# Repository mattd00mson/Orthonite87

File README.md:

# Orthonite87
Orthonite87 is a 87 key Ortholinear keyboard.

## Subheader

Unlock the full potential of ortholinear

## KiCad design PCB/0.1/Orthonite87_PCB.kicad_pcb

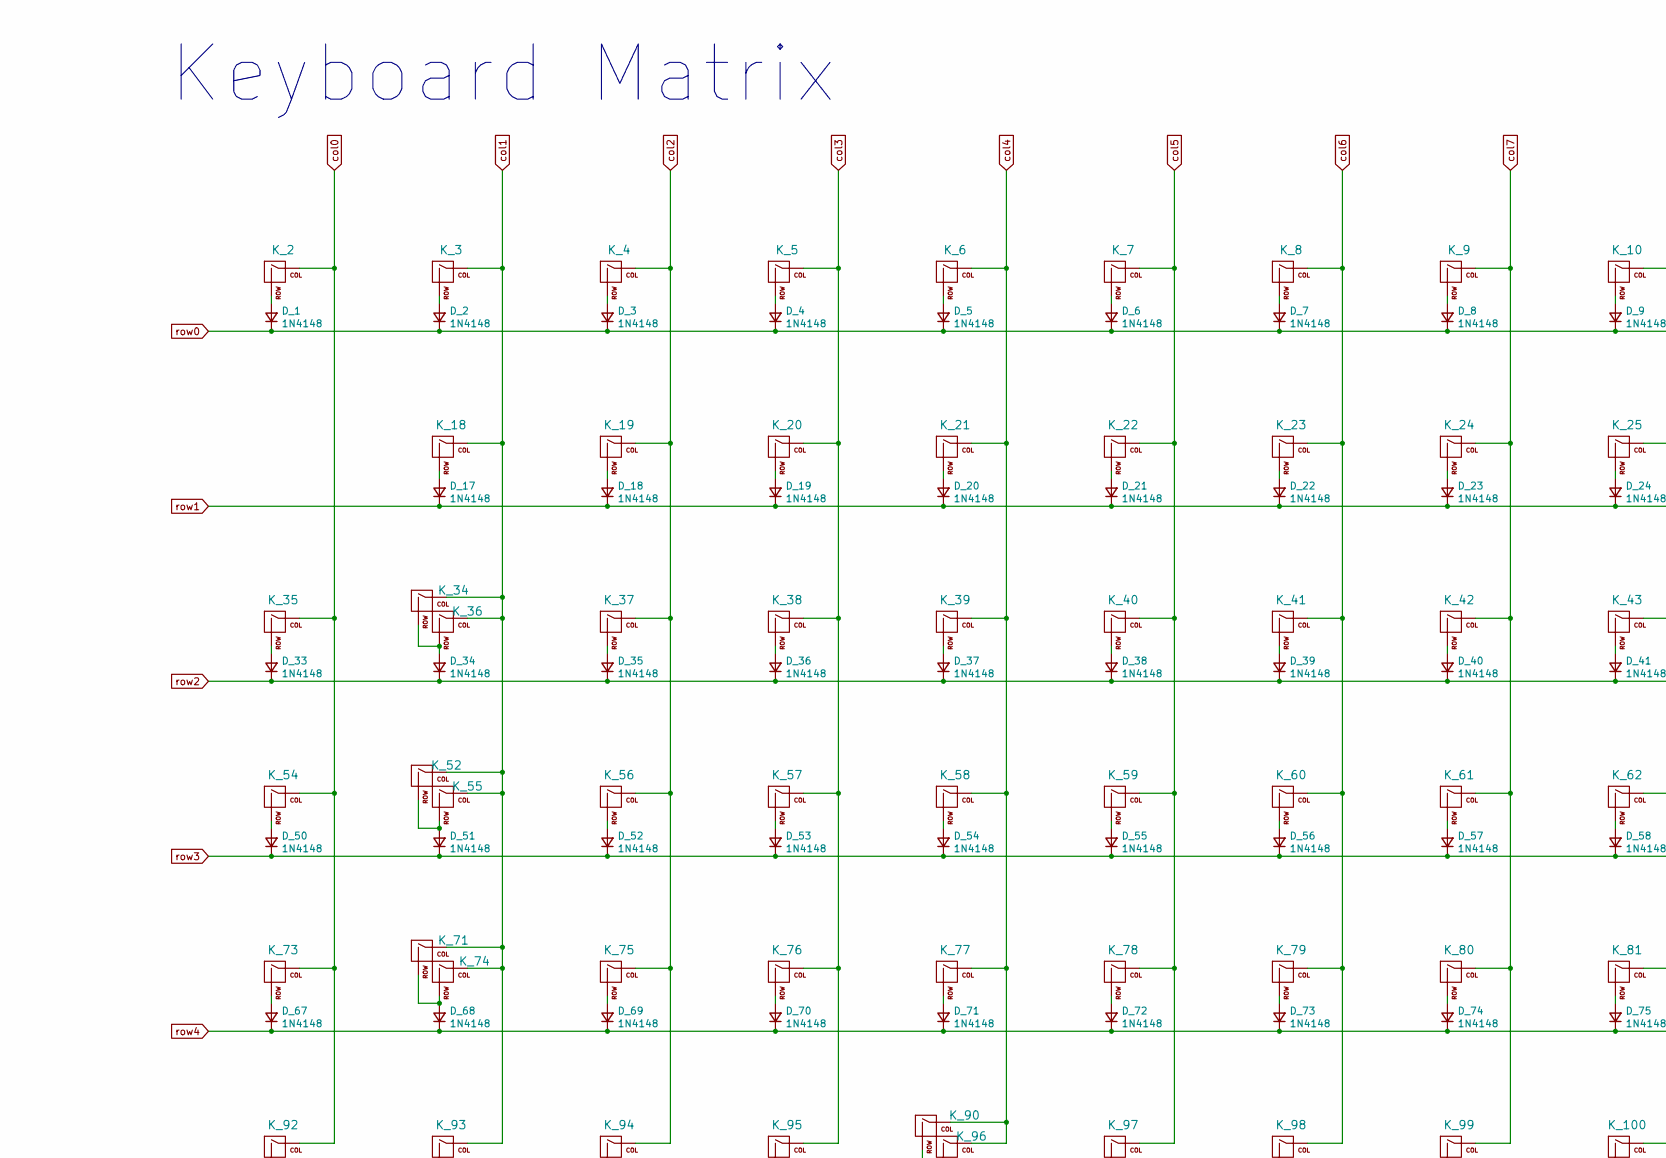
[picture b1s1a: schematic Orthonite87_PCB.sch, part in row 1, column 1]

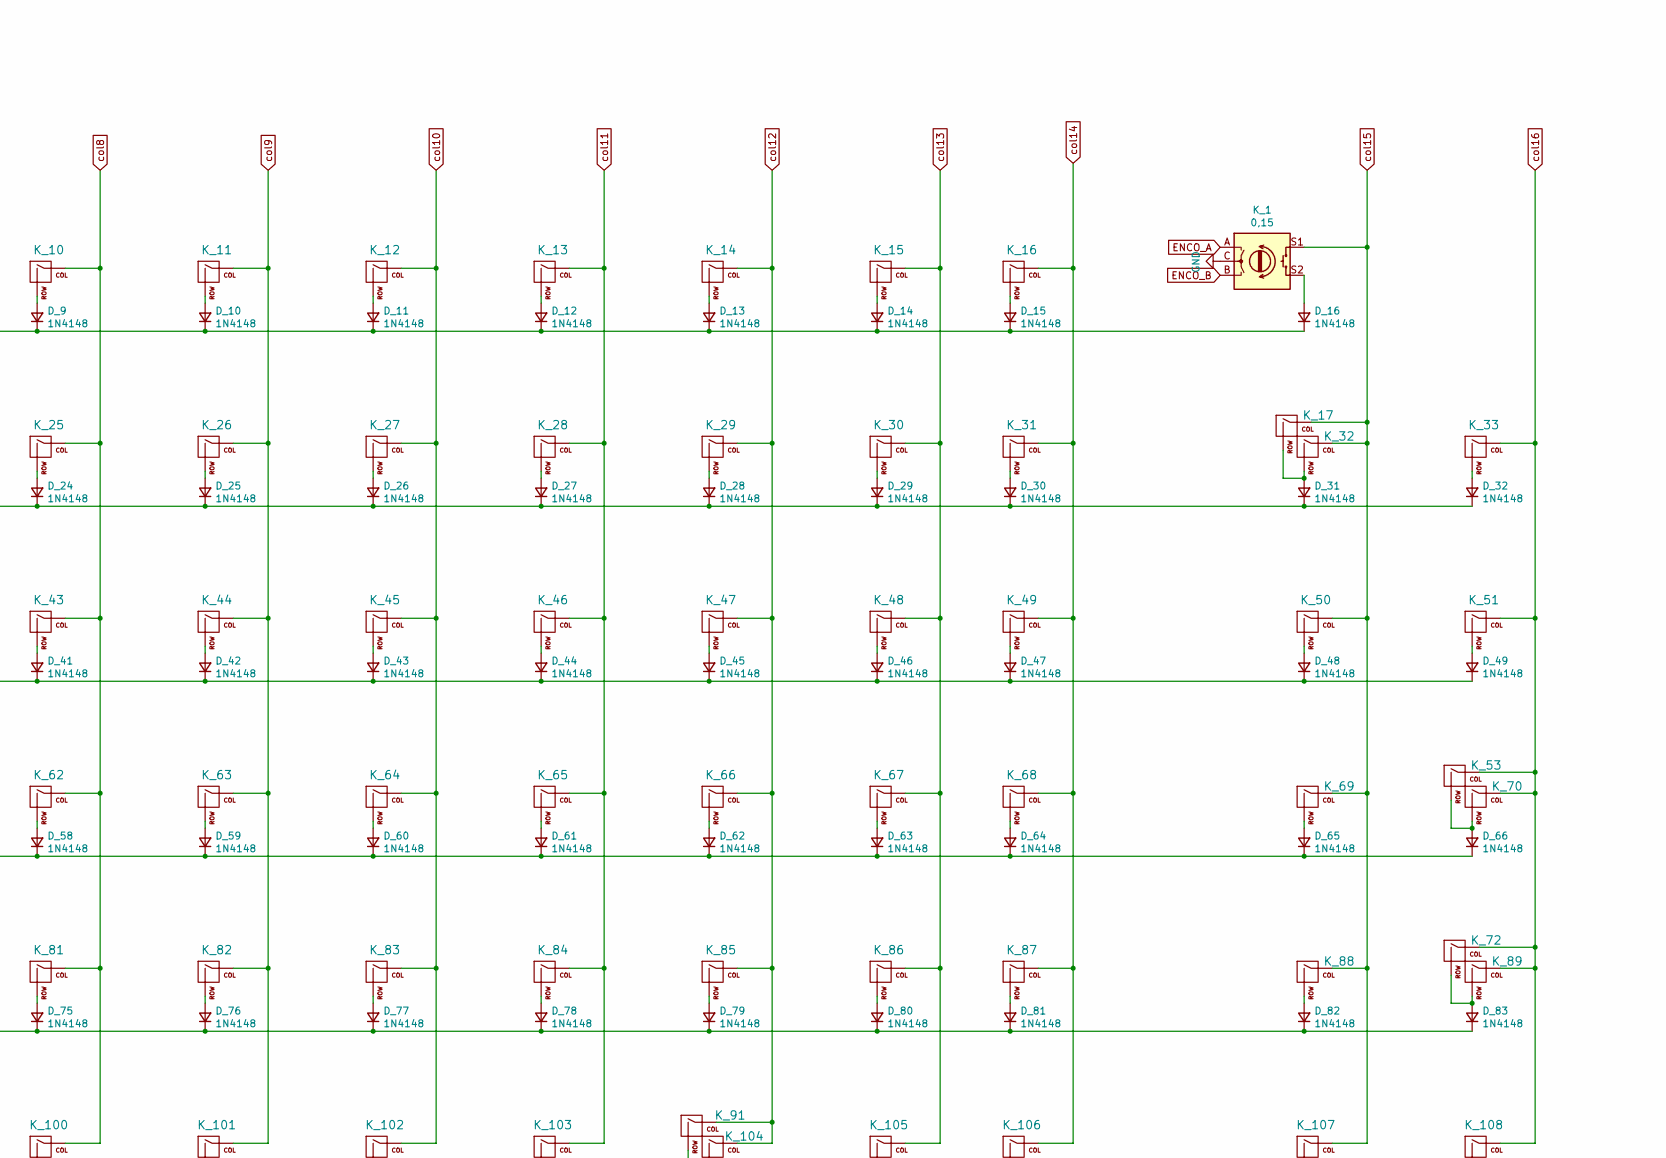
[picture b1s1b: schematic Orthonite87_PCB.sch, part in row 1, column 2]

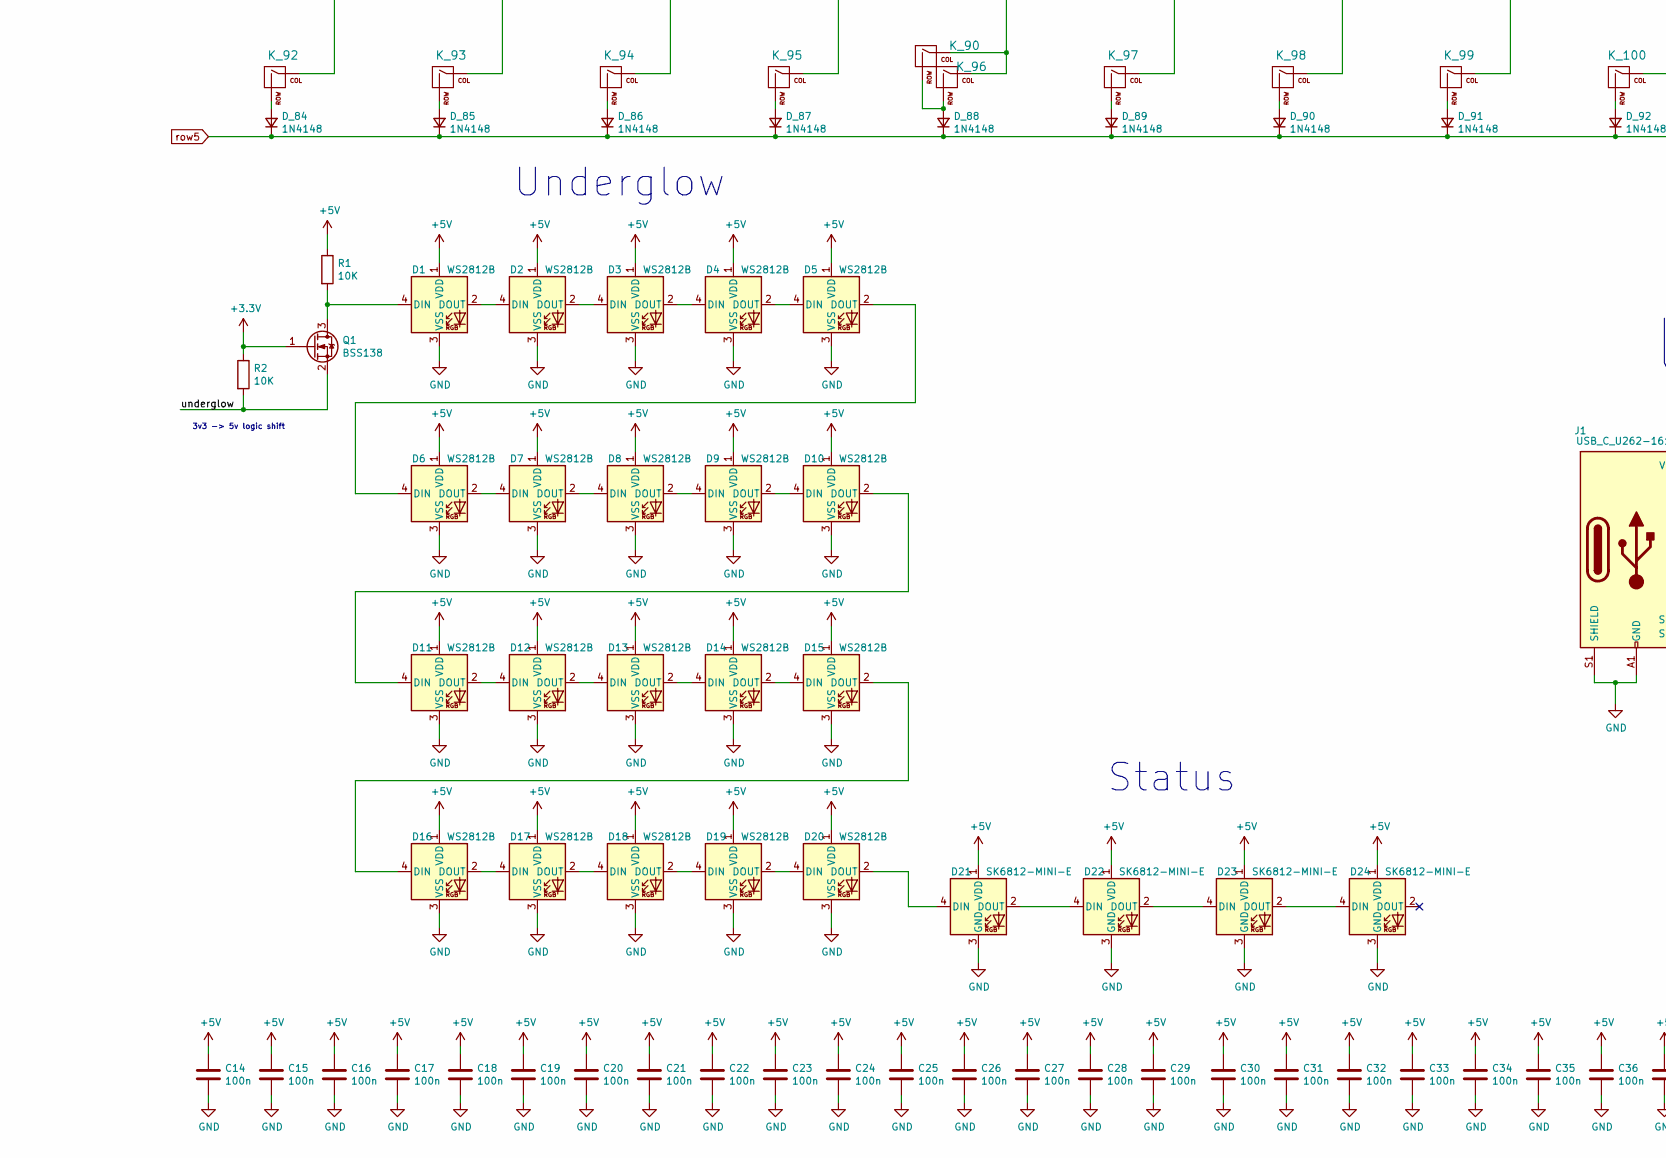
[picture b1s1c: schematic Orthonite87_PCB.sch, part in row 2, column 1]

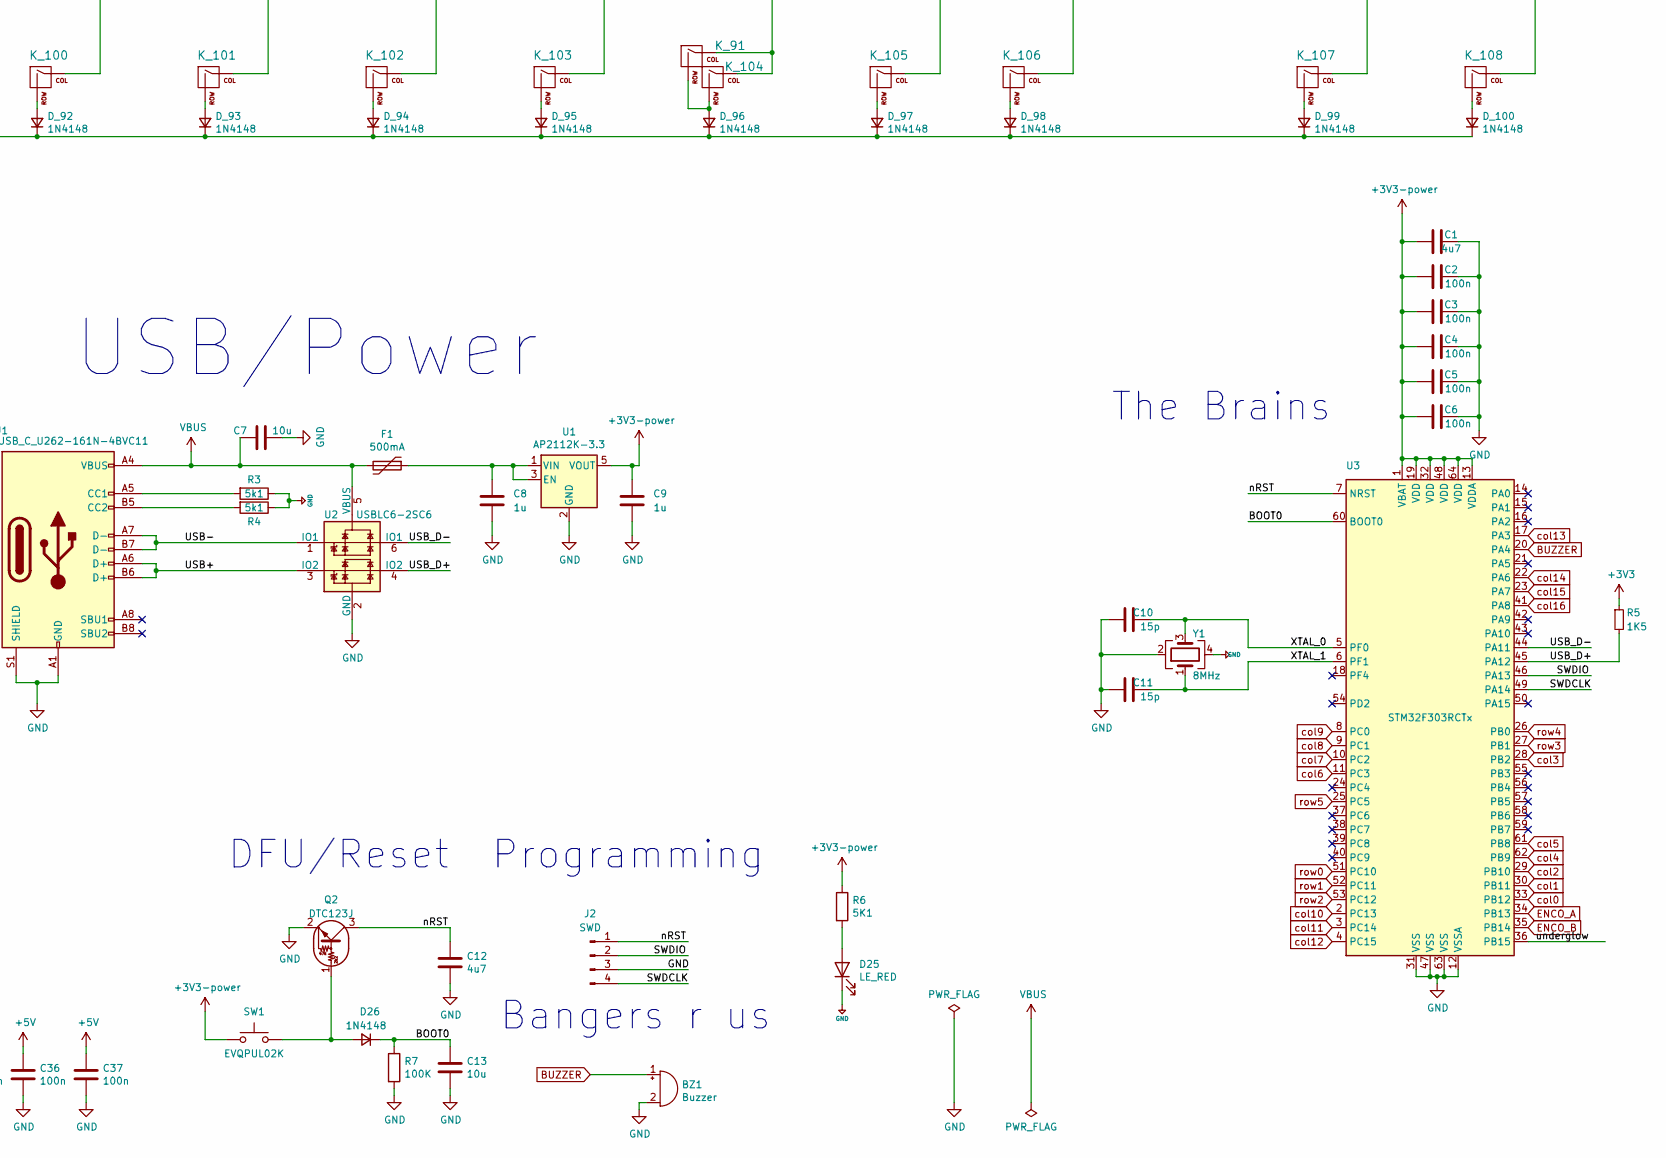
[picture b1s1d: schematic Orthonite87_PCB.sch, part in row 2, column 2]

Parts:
BZ1: Buzzer; Buzzer_Murata_PKMCS0909E4000-R1; MPN PKMCS0909E4000-R1; LCSC C910763
C1, C12: 4u7; C_1608; MPN CL10A475KO8NNNC; JLCSMT C19666
C2, C3, C4, C5, C6: 100n; C_1608; MPN CC0603KRX7R9BB104; JLCSMT C14663
C7, C13: 10u; C_1608; MPN CL10A106KP8NNNC; JLCSMT C19702
C8, C9: 1u; C_1608; MPN CL10A105KB8NNNC; LCSC C15849
C10, C11: 15p; C_1608; MPN CL10C150JB8NNNC; JLCSMT C1644
C14, C15, C16, C17, C18, C19, C20, C21, C22, C23, C24, C25, C26, C27, C28, C29, C30, C31, C32, C33, C34, C35, C36, C37: 100n; C_1608; MPN CC0603KRX7R9BB104; LCSC C14663
D1, D2, D3, D4, D5, D6, D7, D8, D9, D10, D11, D12, D13, D14, D15, D16, D17, D18, D19, D20: WS2812B; LED_WS2812B_PLCC4_5.0x5.0mm_P3.2mm; MPN WS2812B-B; LCSC C114586
D21, D22, D23, D24: SK6812-MINI-E; SK8612-MINI-E; MPN SK6812-MINI-E
D25: LE_RED; LED_0603_1608Metric_45_noSilk; MPN KT-0603R; JLCSMT C2286
D26: 1N4148; SOD3716X135N; MPN 1N4148W; JLCSMT C81598
D_1, D_2, D_3, D_4, D_5, D_6, D_7, D_8, D_9, D_10, D_11, D_12, D_13, D_14, D_15, D_16, D_17, D_18, D_19, D_20, D_21, D_22, D_23, D_24, D_25, D_26, D_27, D_28, D_29, D_30, D_31, D_32, D_33, D_34, D_35, D_36, D_37, D_38, D_39, D_40, D_41, D_42, D_43, D_44, D_45, D_46, D_47, D_48, D_49, D_50, D_51, D_52, D_53, D_54, D_55, D_56, D_57, D_58, D_59, D_60, D_61, D_62, D_63, D_64, D_65, D_66, D_67, D_68, D_69, D_70, D_71, D_72, D_73, D_74, D_75, D_76, D_77, D_78, D_79, D_80, D_81, D_82, D_83, D_84, D_85, D_86, D_87, D_88, D_89, D_90, D_91, D_92, D_93, D_94, D_95, D_96, D_97, D_98, D_99, D_100: 1N4148; SOD3716X135N; MPN 1N4148W; JLCSMT C81598
F1: 500mA; Fuse_0805_2012Metric; MPN SMD0805-050; JLCSMT C66452
J1: USB_C_U262-161N-4BVC11; MPN U262-161N-4BVC11; LCSC C319148
J2: SWD; STM_4_PIN_THT_Staggered
K_1: 0,15; MX_KEYSWITCH_ENCODER
K_2: 0,0; MXOnly-1U-NoLED
K_3: 0,1; MXOnly-1U-NoLED
K_4: 0,2; MXOnly-1U-NoLED
K_5: 0,3; MXOnly-1U-NoLED
K_6: 0,4; MXOnly-1U-NoLED
K_7: 0,5; MXOnly-1U-NoLED
K_8: 0,6; MXOnly-1U-NoLED
K_9: 0,7; MXOnly-1U-NoLED
K_10: 0,8; MXOnly-1U-NoLED
K_11: 0,9; MXOnly-1U-NoLED
K_12: 0,10; MXOnly-1U-NoLED
K_13: 0,11; MXOnly-1U-NoLED
K_14: 0,12; MXOnly-1U-NoLED
K_15: 0,13; MXOnly-1U-NoLED
K_16: 0,14; MXOnly-1U-NoLED
K_17: 1,15; MXOnly-1U-NoLED
K_18: 1,1; MXOnly-1U-NoLED
K_19: 1,2; MXOnly-1U-NoLED
K_20: 1,3; MXOnly-1U-NoLED
K_21: 1,4; MXOnly-1U-NoLED
K_22: 1,5; MXOnly-1U-NoLED
K_23: 1,6; MXOnly-1U-NoLED
K_24: 1,7; MXOnly-1U-NoLED
K_25: 1,8; MXOnly-1U-NoLED
K_26: 1,9; MXOnly-1U-NoLED
K_27: 1,10; MXOnly-1U-NoLED
K_28: 1,11; MXOnly-1U-NoLED
K_29: 1,12; MXOnly-1U-NoLED
K_30: 1,13; MXOnly-1U-NoLED
K_31: 1,14; MXOnly-1U-NoLED
K_32: 1,16; MXOnly-2U-NoLED
K_33: 1,17; MXOnly-1U-NoLED
K_34: 2,1; MXOnly-1U-NoLED
K_35: 2,0; MXOnly-1U-NoLED
K_36: 2,2; MXOnly-2U-NoLED
K_37: 2,3; MXOnly-1U-NoLED
K_38: 2,4; MXOnly-1U-NoLED
K_39: 2,5; MXOnly-1U-NoLED
K_40: 2,6; MXOnly-1U-NoLED
K_41: 2,7; MXOnly-1U-NoLED
K_42: 2,8; MXOnly-1U-NoLED
K_43: 2,9; MXOnly-1U-NoLED
K_44: 2,10; MXOnly-1U-NoLED
K_45: 2,11; MXOnly-1U-NoLED
K_46: 2,12; MXOnly-1U-NoLED
K_47: 2,13; MXOnly-1U-NoLED
K_48: 2,14; MXOnly-1U-NoLED
K_49: 2,15; MXOnly-1U-NoLED
K_50: 2,16; MXOnly-1U-NoLED
K_51: 2,17; MXOnly-1U-NoLED
K_52: 3,1; MXOnly-1U-NoLED
K_53: 3,17; MXOnly-1U-NoLED
K_54: 3,0; MXOnly-1U-NoLED
K_55: 3,2; MXOnly-2U-NoLED
K_56: 3,3; MXOnly-1U-NoLED
K_57: 3,4; MXOnly-1U-NoLED
K_58: 3,5; MXOnly-1U-NoLED
K_59: 3,6; MXOnly-1U-NoLED
K_60: 3,7; MXOnly-1U-NoLED
K_61: 3,8; MXOnly-1U-NoLED
K_62: 3,9; MXOnly-1U-NoLED
K_63: 3,10; MXOnly-1U-NoLED
K_64: 3,11; MXOnly-1U-NoLED
K_65: 3,12; MXOnly-1U-NoLED
K_66: 3,13; MXOnly-1U-NoLED
K_67: 3,14; MXOnly-1U-NoLED
K_68: 3,15; MXOnly-1U-NoLED
K_69: 3,16; MXOnly-1U-NoLED
K_70: 3,18; MXOnly-2U-NoLED
K_71: 4,1; MXOnly-1U-NoLED
K_72: 4,17; MXOnly-1U-NoLED
K_73: 4,0; MXOnly-1U-NoLED
K_74: 4,2; MXOnly-2U-NoLED
K_75: 4,3; MXOnly-1U-NoLED
K_76: 4,4; MXOnly-1U-NoLED
K_77: 4,5; MXOnly-1U-NoLED
K_78: 4,6; MXOnly-1U-NoLED
K_79: 4,7; MXOnly-1U-NoLED
K_80: 4,8; MXOnly-1U-NoLED
K_81: 4,9; MXOnly-1U-NoLED
K_82: 4,10; MXOnly-1U-NoLED
K_83: 4,11; MXOnly-1U-NoLED
K_84: 4,12; MXOnly-1U-NoLED
K_85: 4,13; MXOnly-1U-NoLED
K_86: 4,14; MXOnly-1U-NoLED
K_87: 4,15; MXOnly-1U-NoLED
K_88: 4,16; MXOnly-1U-NoLED
K_89: 4,18; MXOnly-2U-NoLED
K_90: 5,4; MXOnly-1U-NoLED
K_91: 5,13; MXOnly-1U-NoLED
K_92: 5,0; MXOnly-1U-NoLED
K_93: 5,1; MXOnly-1U-NoLED
K_94: 5,2; MXOnly-1U-NoLED
K_95: 5,3; MXOnly-1U-NoLED
K_96: 5,5; MXOnly-3U-ReversedStabilizers-NoLED
K_97: 5,6; MXOnly-1U-NoLED
K_98: 5,7; MXOnly-1U-NoLED
K_99: 5,8; MXOnly-1U-NoLED
K_100: 5,9; MXOnly-1U-NoLED
K_101: 5,10; MXOnly-1U-NoLED
K_102: 5,11; MXOnly-1U-NoLED
K_103: 5,12; MXOnly-1U-NoLED
K_104: 5,14; MXOnly-3U-ReversedStabilizers-NoLED
K_105: 5,15; MXOnly-1U-NoLED
K_106: 5,16; MXOnly-1U-NoLED
K_107: 5,17; MXOnly-1U-NoLED
K_108: 5,18; MXOnly-1U-NoLED
Q1: BSS138; SOT-23; MPN BSS138LT1G; LCSC C82045
Q2: DTC123J; SOT95P280X100-3N; MPN DTC123JKAT146; JLCSMT C111724
R1, R2: 10K; R_1608; MPN 0603WAF1002T5E; LCSC C25804
R3, R4: 5k1; R_1608; MPN 0603WAF5101T5E; JLCSMT C23186
R5: 1K5; R_0603_1608Metric
R6: 5K1; R_1608; MPN 0603WAF5101T5E; JLCSMT C23186
R7: 100K; R_1608; MPN 0603WAF1003T5E; JLCSMT C25803
SW1: EVQPUL02K; Panasonic_EVQPUL_EVQPUC; MPN EVQPUL02K; LCSC C79175
U1: AP2112K-3.3; SOT-23-5; MPN AP2112K-3.3TRG1; LCSC C51118
U2: USBLC6-2SC6; SOT-23-6; MPN USBLC6-2SC6; JLCSMT C7519
U3: STM32F303RCTx; LQFP-64_10x10mm_P0.5mm; MPN Manufacturer; JLCSMT C65361
Y1: 8MHz; Crystal_SMD_3225-4Pin_3.2x2.5mm; MPN TAXM8M4RFDCET2T; JLCSMT C403948

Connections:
/BOOT0: C13.1, D26.1 (K), R7.1, U3.60 (BOOT0)
/SWDCLK: J2.4, U3.49 (PA14)
/SWDIO: J2.2, U3.46 (PA13)
/USB+: J1.A6 (D+), J1.B6 (D+), U2.3 (IO2)
/USB-: J1.A7 (D-), J1.B7 (D-), U2.1 (IO1)
/USB_D+: R5.2, U2.4 (IO2), U3.45 (PA12)
/USB_D-: U2.6 (IO1), U3.44 (PA11)
/XTAL_0: C10.1, U3.5 (PF0), Y1.3; also elsewhere on the board
/XTAL_1: C11.1, U3.6 (PF1), Y1.1; also elsewhere on the board
/nRST: C12.1, J2.1, Q2.3 (C), U3.7 (NRST)
/underglow: Q1.2 (S), R2.2, U3.36 (PB15)
BUZZER: BZ1.1 (-), U3.20 (PA4)
ENCO_A: K_1.A, U3.34 (PB13)
ENCO_B: K_1.B, U3.35 (PB14)
unnamed: C8.2, F1.1, U1.1 (VIN), U1.3 (EN)
unnamed: D1.2 (DOUT), D2.4 (DIN)
unnamed: D1.4 (DIN), Q1.3 (D), R1.2
unnamed: D2.2 (DOUT), D3.4 (DIN)
unnamed: D3.2 (DOUT), D4.4 (DIN)
unnamed: D4.2 (DOUT), D5.4 (DIN)
unnamed: D5.2 (DOUT), D6.4 (DIN)
unnamed: D6.2 (DOUT), D7.4 (DIN)
unnamed: D7.2 (DOUT), D8.4 (DIN)
unnamed: D8.2 (DOUT), D9.4 (DIN)
unnamed: D10.2 (DOUT), D11.4 (DIN)
unnamed: D9.2 (DOUT), D10.4 (DIN)
unnamed: D11.2 (DOUT), D12.4 (DIN)
unnamed: D12.2 (DOUT), D13.4 (DIN)
unnamed: D13.2 (DOUT), D14.4 (DIN)
unnamed: D14.2 (DOUT), D15.4 (DIN)
unnamed: D15.2 (DOUT), D16.4 (DIN)
unnamed: D16.2 (DOUT), D17.4 (DIN)
unnamed: D17.2 (DOUT), D18.4 (DIN)
unnamed: D18.2 (DOUT), D19.4 (DIN)
unnamed: D19.2 (DOUT), D20.4 (DIN)
unnamed: D20.2 (DOUT), D21.4 (DIN)
unnamed: D21.2 (DOUT), D22.4 (DIN)
unnamed: D22.2 (DOUT), D23.4 (DIN)
unnamed: D23.2 (DOUT), D24.4 (DIN)
unnamed: D25.2 (A), R6.2
unnamed: D26.2 (A), Q2.1 (B), SW1.2
unnamed: D_1.2 (A), K_2.2 (ROW)
unnamed: D_2.2 (A), K_3.2 (ROW)
unnamed: D_3.2 (A), K_4.2 (ROW)
unnamed: D_4.2 (A), K_5.2 (ROW)
unnamed: D_5.2 (A), K_6.2 (ROW)
unnamed: D_6.2 (A), K_7.2 (ROW)
unnamed: D_7.2 (A), K_8.2 (ROW)
unnamed: D_8.2 (A), K_9.2 (ROW)
unnamed: D_9.2 (A), K_10.2 (ROW)
unnamed: D_10.2 (A), K_11.2 (ROW)
unnamed: D_11.2 (A), K_12.2 (ROW)
unnamed: D_12.2 (A), K_13.2 (ROW)
unnamed: D_13.2 (A), K_14.2 (ROW)
unnamed: D_14.2 (A), K_15.2 (ROW)
unnamed: D_15.2 (A), K_16.2 (ROW)
unnamed: D_16.2 (A), K_1.S2
unnamed: D_17.2 (A), K_18.2 (ROW)
unnamed: D_18.2 (A), K_19.2 (ROW)
unnamed: D_19.2 (A), K_20.2 (ROW)
unnamed: D_20.2 (A), K_21.2 (ROW)
unnamed: D_21.2 (A), K_22.2 (ROW)
unnamed: D_22.2 (A), K_23.2 (ROW)
unnamed: D_23.2 (A), K_24.2 (ROW)
unnamed: D_24.2 (A), K_25.2 (ROW)
unnamed: D_25.2 (A), K_26.2 (ROW)
unnamed: D_26.2 (A), K_27.2 (ROW)
unnamed: D_27.2 (A), K_28.2 (ROW)
unnamed: D_28.2 (A), K_29.2 (ROW)
unnamed: D_29.2 (A), K_30.2 (ROW)
unnamed: D_30.2 (A), K_31.2 (ROW)
unnamed: D_31.2 (A), K_17.2 (ROW), K_32.2 (ROW)
unnamed: D_32.2 (A), K_33.2 (ROW)
unnamed: D_33.2 (A), K_35.2 (ROW)
unnamed: D_34.2 (A), K_34.2 (ROW), K_36.2 (ROW)
unnamed: D_35.2 (A), K_37.2 (ROW)
unnamed: D_36.2 (A), K_38.2 (ROW)
unnamed: D_37.2 (A), K_39.2 (ROW)
unnamed: D_38.2 (A), K_40.2 (ROW)
unnamed: D_39.2 (A), K_41.2 (ROW)
unnamed: D_40.2 (A), K_42.2 (ROW)
unnamed: D_41.2 (A), K_43.2 (ROW)
unnamed: D_42.2 (A), K_44.2 (ROW)
unnamed: D_43.2 (A), K_45.2 (ROW)
unnamed: D_44.2 (A), K_46.2 (ROW)
unnamed: D_45.2 (A), K_47.2 (ROW)
unnamed: D_46.2 (A), K_48.2 (ROW)
unnamed: D_47.2 (A), K_49.2 (ROW)
unnamed: D_48.2 (A), K_50.2 (ROW)
unnamed: D_49.2 (A), K_51.2 (ROW)
unnamed: D_50.2 (A), K_54.2 (ROW)
unnamed: D_51.2 (A), K_52.2 (ROW), K_55.2 (ROW)
unnamed: D_52.2 (A), K_56.2 (ROW)
unnamed: D_53.2 (A), K_57.2 (ROW)
unnamed: D_54.2 (A), K_58.2 (ROW)
unnamed: D_55.2 (A), K_59.2 (ROW)
unnamed: D_56.2 (A), K_60.2 (ROW)
unnamed: D_57.2 (A), K_61.2 (ROW)
unnamed: D_58.2 (A), K_62.2 (ROW)
unnamed: D_59.2 (A), K_63.2 (ROW)
unnamed: D_60.2 (A), K_64.2 (ROW)
unnamed: D_61.2 (A), K_65.2 (ROW)
unnamed: D_62.2 (A), K_66.2 (ROW)
unnamed: D_63.2 (A), K_67.2 (ROW)
unnamed: D_64.2 (A), K_68.2 (ROW)
unnamed: D_65.2 (A), K_69.2 (ROW)
unnamed: D_66.2 (A), K_53.2 (ROW), K_70.2 (ROW)
unnamed: D_67.2 (A), K_73.2 (ROW)
unnamed: D_68.2 (A), K_71.2 (ROW), K_74.2 (ROW)
unnamed: D_69.2 (A), K_75.2 (ROW)
unnamed: D_70.2 (A), K_76.2 (ROW)
unnamed: D_71.2 (A), K_77.2 (ROW)
unnamed: D_72.2 (A), K_78.2 (ROW)
unnamed: D_73.2 (A), K_79.2 (ROW)
unnamed: D_74.2 (A), K_80.2 (ROW)
unnamed: D_75.2 (A), K_81.2 (ROW)
unnamed: D_76.2 (A), K_82.2 (ROW)
unnamed: D_77.2 (A), K_83.2 (ROW)
unnamed: D_78.2 (A), K_84.2 (ROW)
unnamed: D_79.2 (A), K_85.2 (ROW)
unnamed: D_80.2 (A), K_86.2 (ROW)
unnamed: D_81.2 (A), K_87.2 (ROW)
unnamed: D_82.2 (A), K_88.2 (ROW)
unnamed: D_83.2 (A), K_72.2 (ROW), K_89.2 (ROW)
unnamed: D_84.2 (A), K_92.2 (ROW)
unnamed: D_85.2 (A), K_93.2 (ROW)
unnamed: D_86.2 (A), K_94.2 (ROW)
unnamed: D_87.2 (A), K_95.2 (ROW)
unnamed: D_88.2 (A), K_90.2 (ROW), K_96.2 (ROW)
unnamed: D_89.2 (A), K_97.2 (ROW)
unnamed: D_90.2 (A), K_98.2 (ROW)
unnamed: D_91.2 (A), K_99.2 (ROW)
unnamed: D_92.2 (A), K_100.2 (ROW)
unnamed: D_93.2 (A), K_101.2 (ROW)
unnamed: D_94.2 (A), K_102.2 (ROW)
unnamed: D_95.2 (A), K_103.2 (ROW)
unnamed: D_96.2 (A), K_91.2 (ROW), K_104.2 (ROW)
unnamed: D_97.2 (A), K_105.2 (ROW)
unnamed: D_98.2 (A), K_106.2 (ROW)
unnamed: D_99.2 (A), K_107.2 (ROW)
unnamed: D_100.2 (A), K_108.2 (ROW)
unnamed: J1.A5 (CC1), R3.2
unnamed: J1.B5 (CC2), R4.2
VBUS: C7.2, F1.2, J1.A4 (VBUS), J1.A9 (VBUS), J1.B4 (VBUS), J1.B9 (VBUS), U2.5 (VBUS)
col0: K_2.1 (COL), K_35.1 (COL), K_54.1 (COL), K_73.1 (COL), K_92.1 (COL), U3.33 (PB12)
col1: K_3.1 (COL), K_18.1 (COL), K_34.1 (COL), K_36.1 (COL), K_52.1 (COL), K_55.1 (COL), K_71.1 (COL), K_74.1 (COL), K_93.1 (COL), U3.30 (PB11)
col2: K_4.1 (COL), K_19.1 (COL), K_37.1 (COL), K_56.1 (COL), K_75.1 (COL), K_94.1 (COL), U3.29 (PB10)
col3: K_5.1 (COL), K_20.1 (COL), K_38.1 (COL), K_57.1 (COL), K_76.1 (COL), K_95.1 (COL), U3.28 (PB2)
col4: K_6.1 (COL), K_21.1 (COL), K_39.1 (COL), K_58.1 (COL), K_77.1 (COL), K_90.1 (COL), K_96.1 (COL), U3.62 (PB9)
col5: K_7.1 (COL), K_22.1 (COL), K_40.1 (COL), K_59.1 (COL), K_78.1 (COL), K_97.1 (COL), U3.61 (PB8)
col6: K_8.1 (COL), K_23.1 (COL), K_41.1 (COL), K_60.1 (COL), K_79.1 (COL), K_98.1 (COL), U3.11 (PC3)
col7: K_9.1 (COL), K_24.1 (COL), K_42.1 (COL), K_61.1 (COL), K_80.1 (COL), K_99.1 (COL), U3.10 (PC2)
col8: K_10.1 (COL), K_25.1 (COL), K_43.1 (COL), K_62.1 (COL), K_81.1 (COL), K_100.1 (COL), U3.9 (PC1)
col9: K_11.1 (COL), K_26.1 (COL), K_44.1 (COL), K_63.1 (COL), K_82.1 (COL), K_101.1 (COL), U3.8 (PC0)
col10: K_12.1 (COL), K_27.1 (COL), K_45.1 (COL), K_64.1 (COL), K_83.1 (COL), K_102.1 (COL), U3.2 (PC13)
col11: K_13.1 (COL), K_28.1 (COL), K_46.1 (COL), K_65.1 (COL), K_84.1 (COL), K_103.1 (COL), U3.3 (PC14)
col12: K_14.1 (COL), K_29.1 (COL), K_47.1 (COL), K_66.1 (COL), K_85.1 (COL), K_91.1 (COL), K_104.1 (COL), U3.4 (PC15)
col13: K_15.1 (COL), K_30.1 (COL), K_48.1 (COL), K_67.1 (COL), K_86.1 (COL), K_105.1 (COL), U3.17 (PA3)
col14: K_16.1 (COL), K_31.1 (COL), K_49.1 (COL), K_68.1 (COL), K_87.1 (COL), K_106.1 (COL), U3.22 (PA6)
col15: K_1.S1, K_17.1 (COL), K_32.1 (COL), K_50.1 (COL), K_69.1 (COL), K_88.1 (COL), K_107.1 (COL), U3.23 (PA7)
col16: K_33.1 (COL), K_51.1 (COL), K_53.1 (COL), K_70.1 (COL), K_72.1 (COL), K_89.1 (COL), K_108.1 (COL), U3.41 (PA8)
row0: D_1.1 (K), D_2.1 (K), D_3.1 (K), D_4.1 (K), D_5.1 (K), D_6.1 (K), D_7.1 (K), D_8.1 (K), D_9.1 (K), D_10.1 (K), D_11.1 (K), D_12.1 (K), D_13.1 (K), D_14.1 (K), D_15.1 (K), D_16.1 (K), U3.51 (PC10)
row1: D_17.1 (K), D_18.1 (K), D_19.1 (K), D_20.1 (K), D_21.1 (K), D_22.1 (K), D_23.1 (K), D_24.1 (K), D_25.1 (K), D_26.1 (K), D_27.1 (K), D_28.1 (K), D_29.1 (K), D_30.1 (K), D_31.1 (K), D_32.1 (K), U3.52 (PC11)
row2: D_33.1 (K), D_34.1 (K), D_35.1 (K), D_36.1 (K), D_37.1 (K), D_38.1 (K), D_39.1 (K), D_40.1 (K), D_41.1 (K), D_42.1 (K), D_43.1 (K), D_44.1 (K), D_45.1 (K), D_46.1 (K), D_47.1 (K), D_48.1 (K), D_49.1 (K), U3.53 (PC12)
row3: D_50.1 (K), D_51.1 (K), D_52.1 (K), D_53.1 (K), D_54.1 (K), D_55.1 (K), D_56.1 (K), D_57.1 (K), D_58.1 (K), D_59.1 (K), D_60.1 (K), D_61.1 (K), D_62.1 (K), D_63.1 (K), D_64.1 (K), D_65.1 (K), D_66.1 (K), U3.27 (PB1)
row4: D_67.1 (K), D_68.1 (K), D_69.1 (K), D_70.1 (K), D_71.1 (K), D_72.1 (K), D_73.1 (K), D_74.1 (K), D_75.1 (K), D_76.1 (K), D_77.1 (K), D_78.1 (K), D_79.1 (K), D_80.1 (K), D_81.1 (K), D_82.1 (K), D_83.1 (K), U3.26 (PB0)
row5: D_84.1 (K), D_85.1 (K), D_86.1 (K), D_87.1 (K), D_88.1 (K), D_89.1 (K), D_90.1 (K), D_91.1 (K), D_92.1 (K), D_93.1 (K), D_94.1 (K), D_95.1 (K), D_96.1 (K), D_97.1 (K), D_98.1 (K), D_99.1 (K), D_100.1 (K), U3.25 (PC5)

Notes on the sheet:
Keyboard Matrix
USB/Power
DFU/Reset
Programming
Bangers r us
3v3 -> 5v logic shift
Status
Underglow
The Brains

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
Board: 2 copper layers, 289 parts (177 on the bottom side), 170 nets, no tracks yet.

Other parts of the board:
Yw: 8MHz; Crystal_SMD_3225-4Pin_3.2x2.5mm

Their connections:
/XTAL_0: Yw.3; also elsewhere on the board
/XTAL_1: Yw.1; also elsewhere on the board

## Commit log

2021-08-17 Set up directory files
    created plate drawing in auto cad
    set up kicad libraries
2021-08-17 schematic update
    library updates
    general schematic progress
2021-08-17 PCB schematic updates
    add libraries
    schematic progress
2021-08-18 Schematic update
    Near finished with rev0.1
2021-08-19 pcb routing and art
    Finished routing and rev1 of art on pcb
2021-08-20 more updates
    PCB fixes
    Began Modeling
2021-08-21 Updates
    bug fixes
2021-08-27 keyshotadded
2021-08-27 render files
2021-08-29 renderupdates
